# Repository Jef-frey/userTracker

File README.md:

# User tracker using IR sensors
This project contains the software and design to build a device that will rotate in response to the user's hand movement, such that it follows or avoids the user's hand. This is used in a hobby project of mine to add on to a robot model.

## Components
IR transmitters and receivers will be used to detect the user's hand movement, a motor will be used such that the device follows the user's hand. A LED will be used to simulate the eye of the device. And PIC16F15344 will be used to control the signals.

- 1 x PIC16F15344
- 1 x 28BYJ-48 Stepper Motor
- 1 x yellow LED
- 2 x IR receivers
- 2 x IR transmitters
- 3 x 1 kOhm current-limiting resistor
- 2 x 10 kOhm resistor

## Design
A pair of IR transmitter/receiver will be used to create a sensor to detect how close the user's hand is to the device.
Two such sensors will be used to compare the distance of the sensors and the user's hand, and the device will be mounted on a motor to rotate in the direction corresponding to the user's proximity with the sensors. 

https://github.com/user-attachments/assets/1b537696-194a-400e-b10d-6a0f2009ed03

## Configuration
The circuit and PCB will need to be redesigned to add features or change to fit your own project, but if you wish to just try out the design, the PCB can be glued to the motor and it will function as intended.
You may want to change the sensitivity of the device, the steps are as follow:
1. determine locations of the 'rec_1' and 'rec_2' points on your own circuit ('rec_1' and 'rec_2' will be shown at the schematic below)
2. put your hand at the distance for the desired movement detection range and measure the voltage at the 'rec_1' and 'rec_2' points
3. pick the greater voltage value (in mV) from the two points, divide it by 2 and convert it to a binary number, round up the 2 least significant bits and logical right shift by 2
4. change the ADCRESH_REG variable at line 27 at the [main.c](main.c) file to the value from step 3

For example, in my device I measured 363mV  
363mV -> 181.5 -> 0b1011_0101 -> 0b1011_1000 -> 0b0010_1110  
And '0b00101110' is my value for ADCRESH_REG

## Schematic

## Microcontroller requirements
A different microcontroller can be used, but it have to support the following features/peripherals
- timer
- comparator
- PWM (uses a second timer in this example)
- ADC

## How it works
The device has 3 states: IDLE, CW, CCW  
In IDLE state, motor will stop, LED will fade off if it was on(TMR0 will slowly decrement the duty cycle of the PWM). Comparator will be used to compare voltage difference between IR receivers, the change in output will turn on the LED to start fading on(TMR0 will slowly increment the duty cycle of the PWM), and device will enter CW(clockwise) state or CCW(counter-clockwise) state depends on the comparator output.  
In CW state, motor will turn clockwise, and ADC will continuously detect IR receivers' voltage level. Once both receivers' voltage level is lower than specific level for a few cycles (to avoid misread), device will enter IDLE state.  
In CCW state, motor will turn counter-clockwise, all other operations are the same as CW state.

## Possible issues and improvements
- A different sensor was originally used, as the current detection method has very limited range. The first iteration used PIR sensors, but it cannot be used on moving devices and has a ~2 sec delay time after motions stopped so it wasn't used. Upon further research time of flight sensor may be used, but it is more costly and complex.
- To save power in IDLE mode, a sleep function can be implemented
- To save power in IDLE mode, IR transmitter can be turn on for a short interval after a small delay (to have a PWM on the IR transmitter)

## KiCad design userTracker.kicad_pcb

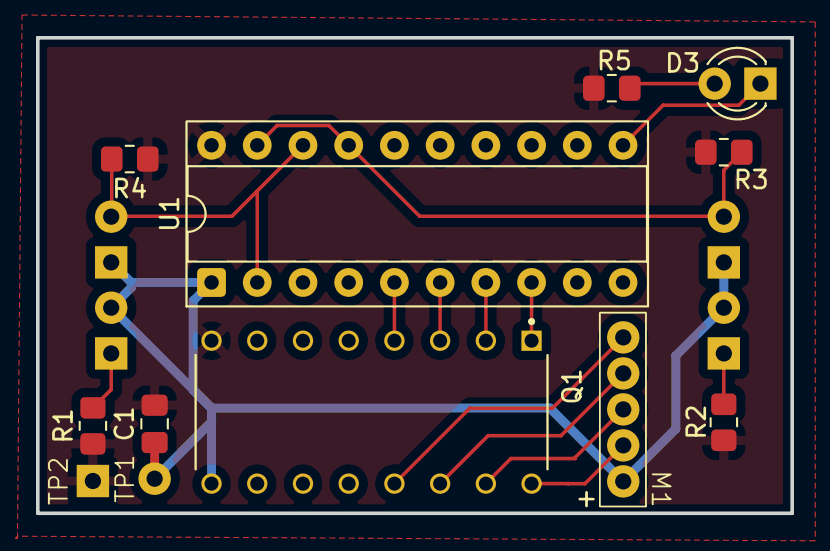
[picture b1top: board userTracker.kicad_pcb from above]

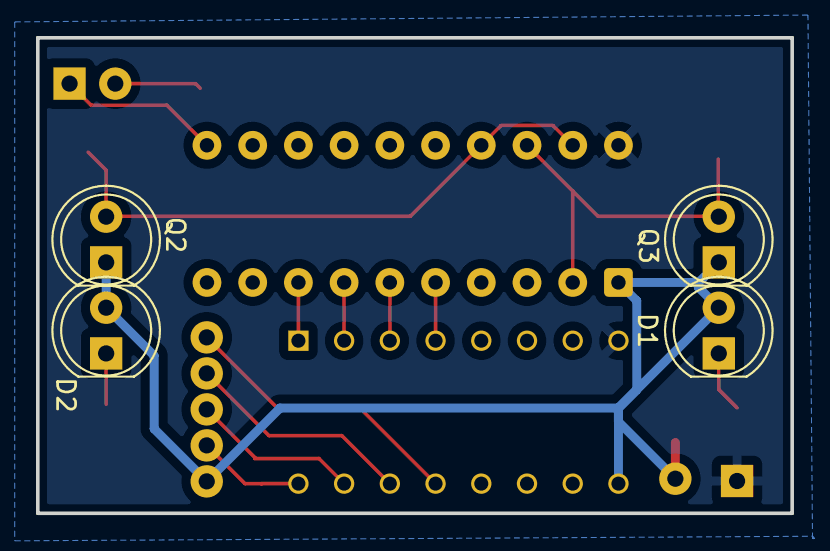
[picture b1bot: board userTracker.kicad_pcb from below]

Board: 2 copper layers, 41.9 x 26.4 mm, 16 parts (4 on the bottom side), 16 nets.

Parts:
C1: 0.1uF; C_0805_2012Metric_Pad1.18x1.45mm_HandSolder
D1, D2: IR transmitter; LED_D5.0mm_Clear
D3: LED; LED_D3.0mm
M1: 28BYJ-48; stepper_motor
Q1: ULN2003AN; DIP794W45P254L1969H508Q16
Q2, Q3: IR receiver; LED_D5.0mm_IRBlack
R1, R2, R5: 1 kOhm; R_0805_2012Metric_Pad1.20x1.40mm_HandSolder
R3, R4: 10 kOhm; R_0805_2012Metric_Pad1.20x1.40mm_HandSolder
TP1, TP2: TestPoint; test_point
U1: PIC16F15344; DIP-20_W7.62mm_Socket

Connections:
+5V: C1.1, D1.2 (A), D2.2 (A), M1.1, Q1.9, Q2.1, Q3.1, TP1.1, U1.1 (VDD)
/PWM: D3.1 (K), U1.11 (RB6)
/RC3: Q1.2, U1.7 (RC3)
/RC4: Q1.3, U1.6 (RC4)
/RC5: Q1.4, U1.5 (RC5)
/RC6: Q1.1, U1.8 (RC6)
/m1: M1.2, Q1.16
/m2: M1.3 (-), Q1.15
/m3: M1.4, Q1.14
/m4: M1.5, Q1.13
/rec_1: Q2.2, R3.2, U1.17 (RA2), U1.19 (RA0/ICSPDAT)
/rec_2: Q3.2, R4.2, U1.2 (RA5), U1.18 (RA1/ICSPCLK)
GND: C1.2, Q1.8 (E), R1.1, R2.1, R3.1, R4.1, R5.2, TP2.1, U1.20 (VSS)
unnamed: D1.1 (K), R1.2
unnamed: D2.1 (K), R2.2
unnamed: D3.2 (A), R5.1

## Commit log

2025-08-14 Update README.md
    backup file
2025-08-14 Update README.md
    Finalized documentation
2025-08-14 Create main.c
    source file
2025-10-06 Update README.md
    Updated README after updating the code
2025-10-06 Update main.c
    Update pin placement and sensor sensitivity level after feedback from installing it onto the robot model.
2026-03-19 Add files via upload
    New ADCRESH_REG value
2026-03-19 Update README.md
    update the pictures
2026-03-19 Update README.md
    Correct grammatical errors
2026-03-19 Add files via upload
    Added the PCB files
2026-04-02 Update README.md
    Updated the video
